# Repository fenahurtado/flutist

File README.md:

# Pierre the Flutist Robot

En este repositorio se encuentra el codigo necesario para operar el sistema robotico para tocar flauta, Pierre.

Organización del codigo
-----
Los archivos de codigo importantes y su contenido:

| File   |     Content     |
|:--------:|-------------|
| cinematica.py |  clases y funciones para pasar del espacio del robot al de la tarea y viceversa  |
| communication.py | Una clase que se encarga de la mensajería a los distintos dispositivos (usando el protocolo Ethernet IP) de forma centralizada |
| drivers.py | Clases que se encargan con la interacción de los distintos dispositivos: controlador de flujo, sensor de presión, drivers de los motores, driver de los dedos y micrófono |
| GUI.py | Codigo de la ventana principal de la interfaz gráfica |
| manual_move_win.py | Código de la ventana para manejar el robot de forma manual |
| motor_route.py | Código para obtener rutas de 'straight lines' en el espacio de la tarea o de polinamios de tercer orden (al final no se usa) |
| musician.py | Donde se aloja la clase Musician, que funciona como cerebro del robot, coordina las solicitudes del usuario con cada uno de los dispositivos |
| route.py | Código para construir rutas definidas a partir de puntos en cada eje (l, theta, offset, flow y nota) en el tiempo, filtros y vibratos |
| forms/forms.py | Codigo para interpretar la información entregada por el usuario en todos los formularios de la interfaz gráfica |
| lib/ethernet_ip/ethernetip.py | Librería modificada para comunicacion mediante protocolo Ethernet IP. Los cambios estan explicados en el encabezado del archivo |
| plots/plot_window.py | Código de las ventanas que plotean funciones, una que se actualiza en tiempo real (una variable vs la referencia) y otra que no (visualización de la ruta definida y las velocidades en cada eje) |

Cada archivo se encuentra comentado para que sea facil su comprension

Adicionalmente se entregan <a href="https://raw.githack.com/fenahurtado/pierre_flutist/cf3378f31c493d1e27e5e798b959a1f9c4f3be40/diagrama.html" target="_blank">diagramas de flujo</a> de todo el codigo para entender mejor su funcionamiento

### PS Move
El programa ocupa el repositorio externo [psmove](https://github.com/thp/psmoveapi).
Este debe ser descargado y se deben hacer los siguientes cambios:
1. Reemplazar el archivo psmoveapi/src/CMakeList.txt por pierre_flutist/src/psmoveapi_mods/CMakeList.txt (o agregar la opcion `option(PSMOVE_BUILD_TRACKER "Enable Tracking" ON)` al CMakeList)
2. Reemplazar el archivo psmoveapi/src/utils/test_tracker.cpp por pierre_flutist/src/psmoveapi_mods/test_tracker.cpp

Luego, se debe compilar el proyecto. Para compilar desde Windows se corre el comando:
`call scripts/visualc/build_msvc.bat 2022 x64` en la *Developer Command Prompt for VS 2022*

Finalmente para correr el script, se corre (dentro de la carpeta del build recien creada) `psmove test-tracker`.

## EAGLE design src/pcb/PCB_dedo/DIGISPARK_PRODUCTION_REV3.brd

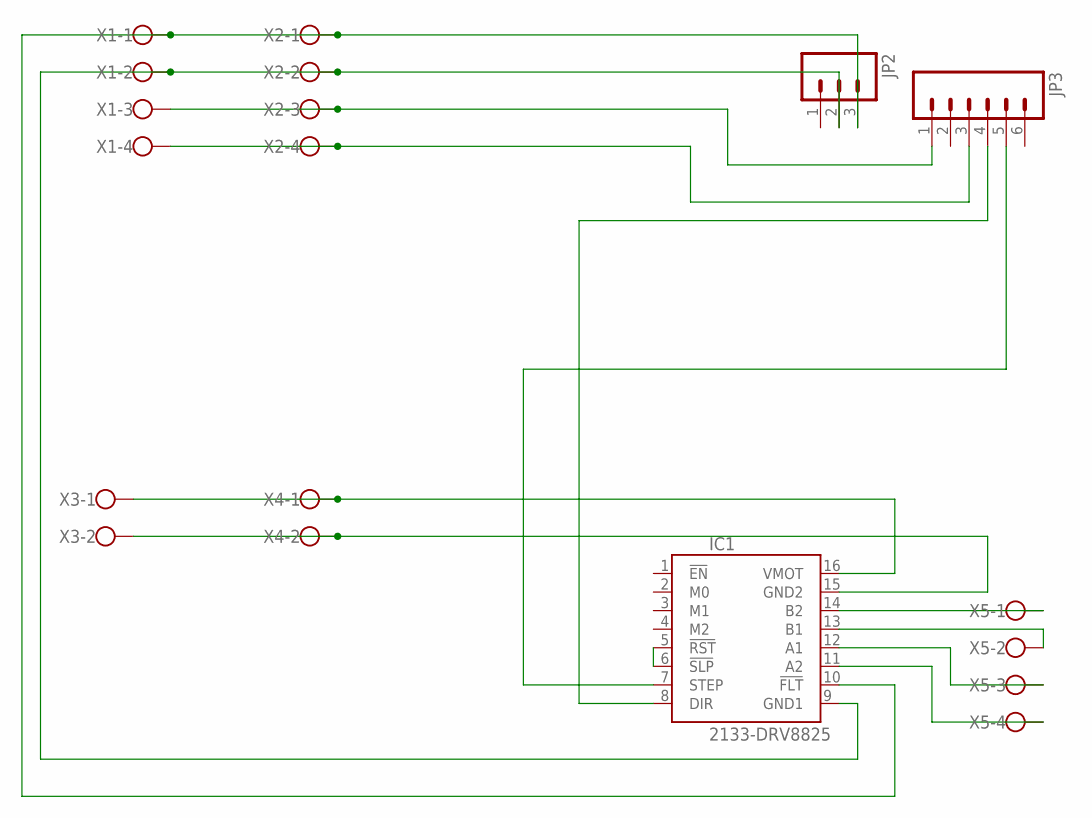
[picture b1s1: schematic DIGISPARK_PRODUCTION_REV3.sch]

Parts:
IC1: 2133-DRV8825; DRV8825
JP2: M03PTH; 1X03
JP3: M06SIP; 1X06
X1, X2, X5: W237-4
X3, X4: W237-102

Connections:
unnamed: IC1.14 (B2), X5.1
unnamed: IC1.13 (B1), X5.2
unnamed: IC1.12 (A1), X5.3
unnamed: IC1.11 (A2), X5.4
unnamed: IC1.10 (!FLT), JP2.3, X1.1, X2.1
unnamed: IC1.9 (GND1), JP2.2, X1.2, X2.2
unnamed: JP3.1, X1.3, X2.3
unnamed: JP3.3, X1.4, X2.4
unnamed: IC1.16 (VMOT), X3.1, X4.1
unnamed: IC1.15 (GND2), X3.2, X4.2
unnamed: IC1.7 (STEP), JP3.5
unnamed: IC1.5 (!RST), IC1.6 (!SLP)
unnamed: IC1.8 (DIR), JP3.4

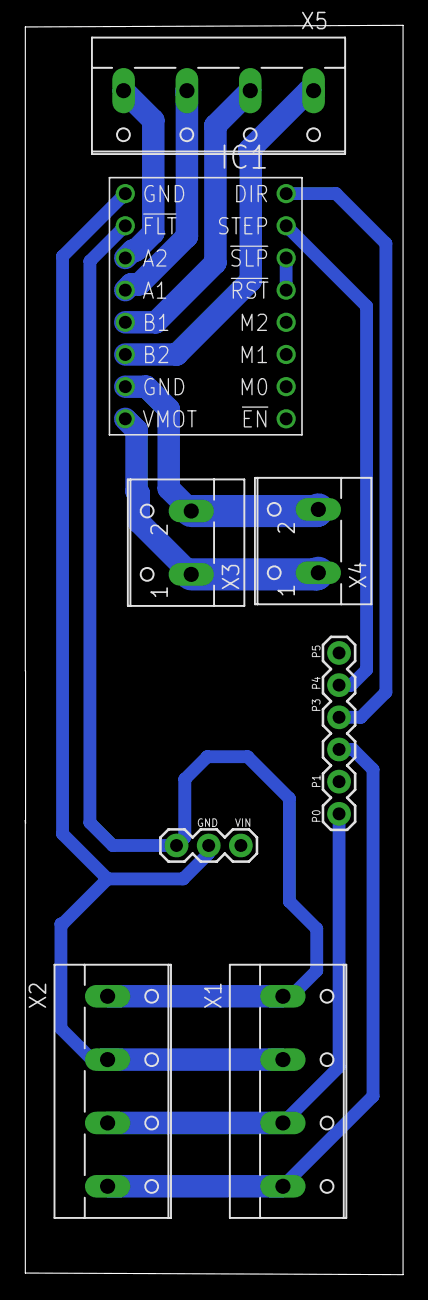
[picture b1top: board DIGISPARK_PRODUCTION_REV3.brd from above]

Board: 2 copper layers, 29.8 x 98.6 mm, 8 parts (0 on the bottom side), 13 nets.

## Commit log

2023-06-14 primer commit
2023-06-20 primer orden del codigo con comentarios reordenado pero sin cambios importantes
2023-06-22 primer push en ubuntu
2023-07-07 cambios al control de los dedos
2023-07-07 cambio de algunos procesos a threads
2023-07-07 agregaron varios comentarios al codigo
2023-07-10 agrega algunos archivos que no son de codigo, y varios comentarios
2023-07-10 drivers.py comentado completo
2023-07-10 agregue psmoveapi y varios comentarios
2023-07-10 Varios comentarios en GUI.py
2023-07-11 added 3d models
2023-07-12 comentarios listos en GUI.py
2023-07-12 comentarios a manual_move_win.py
2023-07-13 comentarios a motor_route.py
2023-07-13 varios comentarios nuevos
2023-07-13 musico comentado completo
2023-07-13 comentarios listos en route.py
2023-07-14 comentarios listos
2023-07-15 mas explicacion y diagramas
2023-07-18 diagrama
2023-07-18 ps move
2023-07-18 psmove
2023-07-19 cambio diagrama, vibrato y etude mecanique
2023-07-19 cambio readme
2023-08-20 primeros cambios para agregar lengua y labios
2024-04-09 traspaso codigo

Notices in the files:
parts and their libraries:
SparkFun: Licensing: CC v3.0 Share-Alike You are welcome to use this library for commercial purposes.
